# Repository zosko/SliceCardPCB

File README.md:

# Slice Card on PCB

### Scheme

### Board

### Preview

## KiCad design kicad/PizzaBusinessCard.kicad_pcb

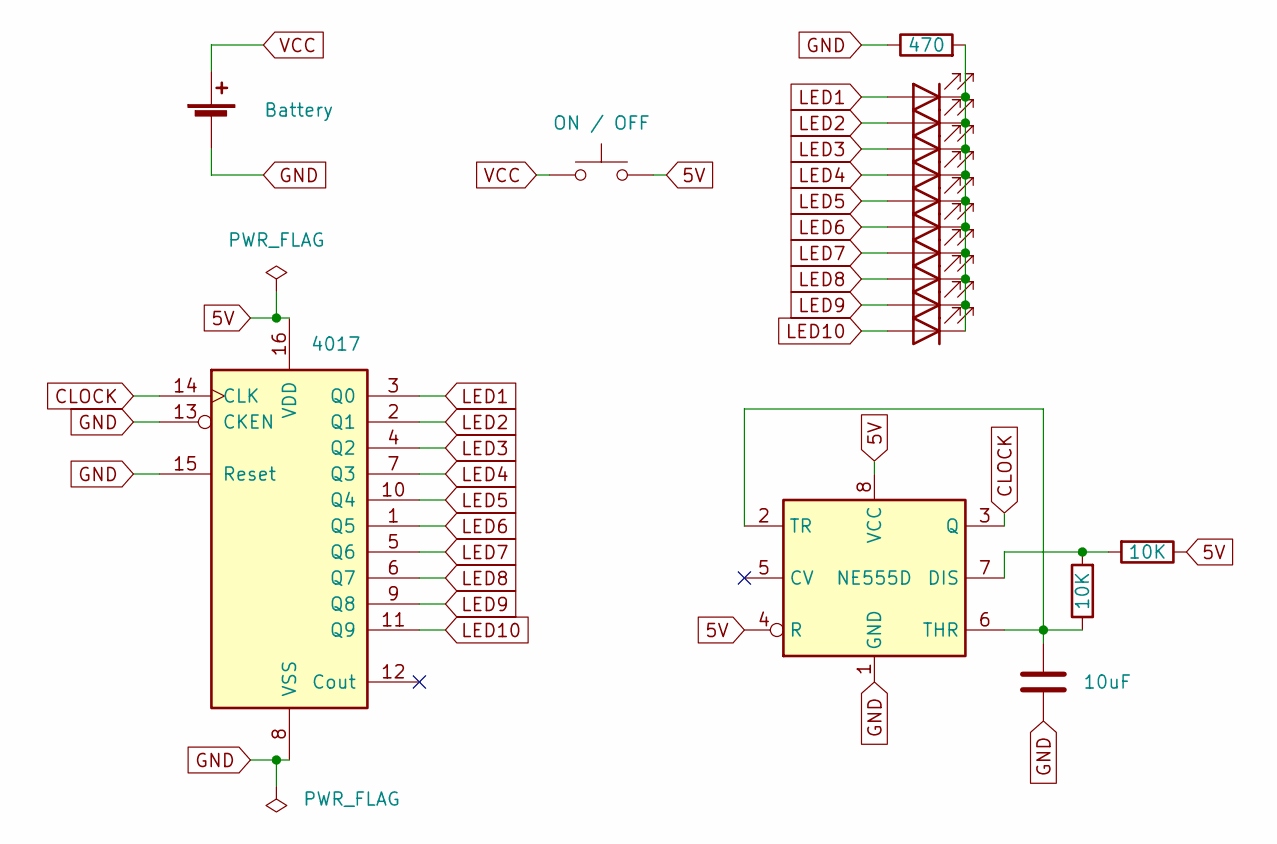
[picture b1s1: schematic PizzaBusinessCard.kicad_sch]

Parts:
BT1: Battery; BatteryHolder_Keystone_3000_1x12mm
C2: 10uF; C_0805_2012Metric_Pad1.18x1.45mm_HandSolder
D2, D3, D4, D5, D6, D7, D8, D9, D10, D11: LED; LED_0805_2012Metric_Pad1.15x1.40mm_HandSolder
R1, R3: 10K; R_0805_2012Metric_Pad1.20x1.40mm_HandSolder
R2: 470; R_0805_2012Metric_Pad1.20x1.40mm_HandSolder
SW1: ON / OFF; SW_SPST_CK_RS282G05A3
U1: 4017; SOIC-16_3.9x9.9mm_P1.27mm
U2: NE555D; SOIC-8_3.9x4.9mm_P1.27mm

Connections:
5V: R1.1, SW1.2, U1.16 (VDD), U2.4 (R), U2.8 (VCC)
CLOCK: U1.14 (CLK), U2.3 (Q)
GND: BT1.2 (-), C2.2, R2.1, U1.8 (VSS), U1.13 (CKEN), U1.15 (Reset), U2.1 (GND)
LED1: D2.2 (A), U1.3 (Q0)
LED2: D3.2 (A), U1.2 (Q1)
LED3: D4.2 (A), U1.4 (Q2)
LED4: D5.2 (A), U1.7 (Q3)
LED5: D6.2 (A), U1.10 (Q4)
LED6: D7.2 (A), U1.1 (Q5)
LED7: D8.2 (A), U1.5 (Q6)
LED8: D9.2 (A), U1.6 (Q7)
LED9: D10.2 (A), U1.9 (Q8)
LED10: D11.2 (A), U1.11 (Q9)
unnamed: C2.1, R3.1, U2.2 (TR), U2.6 (THR)
unnamed: D2.1 (K), D3.1 (K), D4.1 (K), D5.1 (K), D6.1 (K), D7.1 (K), D8.1 (K), D9.1 (K), D10.1 (K), D11.1 (K), R2.2
unnamed: R1.2, R3.2, U2.7 (DIS)
VCC: BT1.1 (+), SW1.1

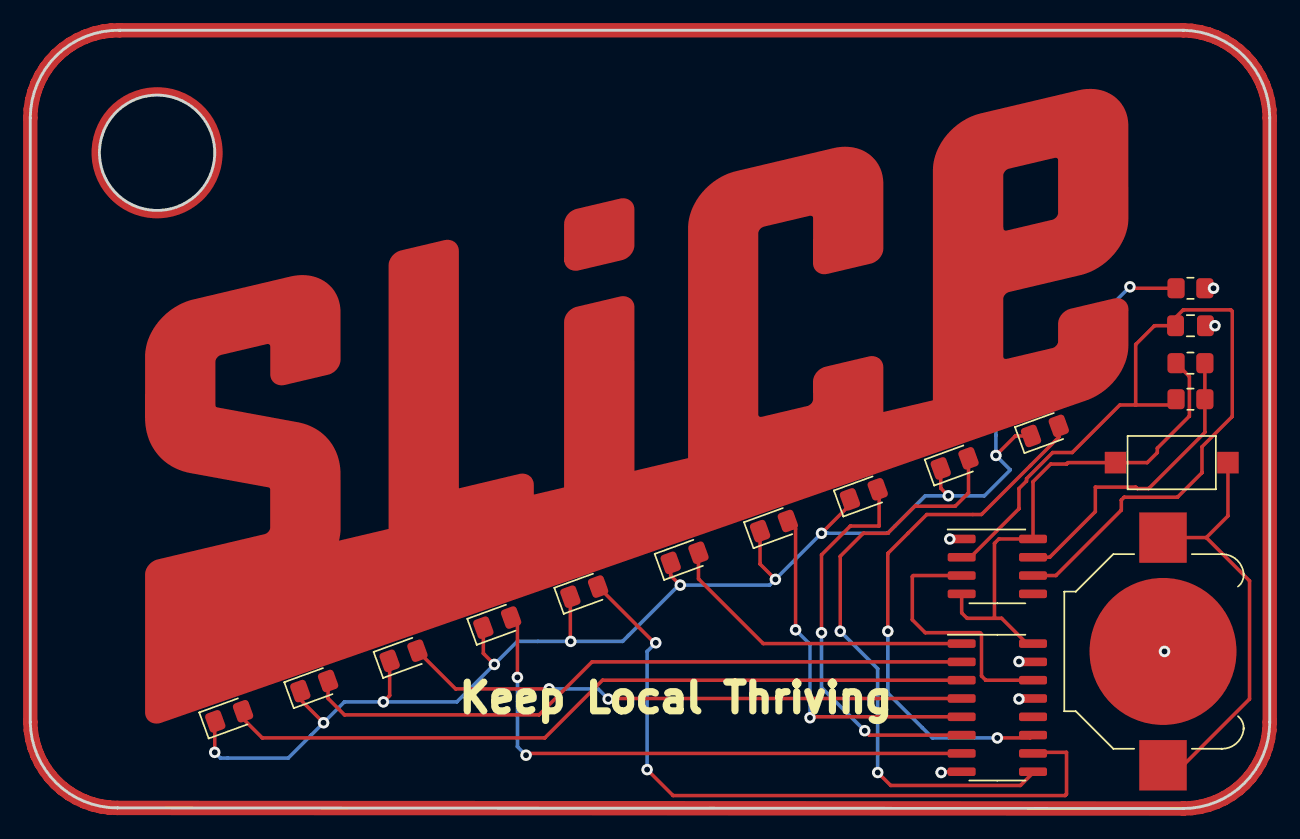
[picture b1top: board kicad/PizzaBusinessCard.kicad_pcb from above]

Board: 2 copper layers, 86.0 x 54.0 mm, 18 parts (0 on the bottom side), 17 nets.

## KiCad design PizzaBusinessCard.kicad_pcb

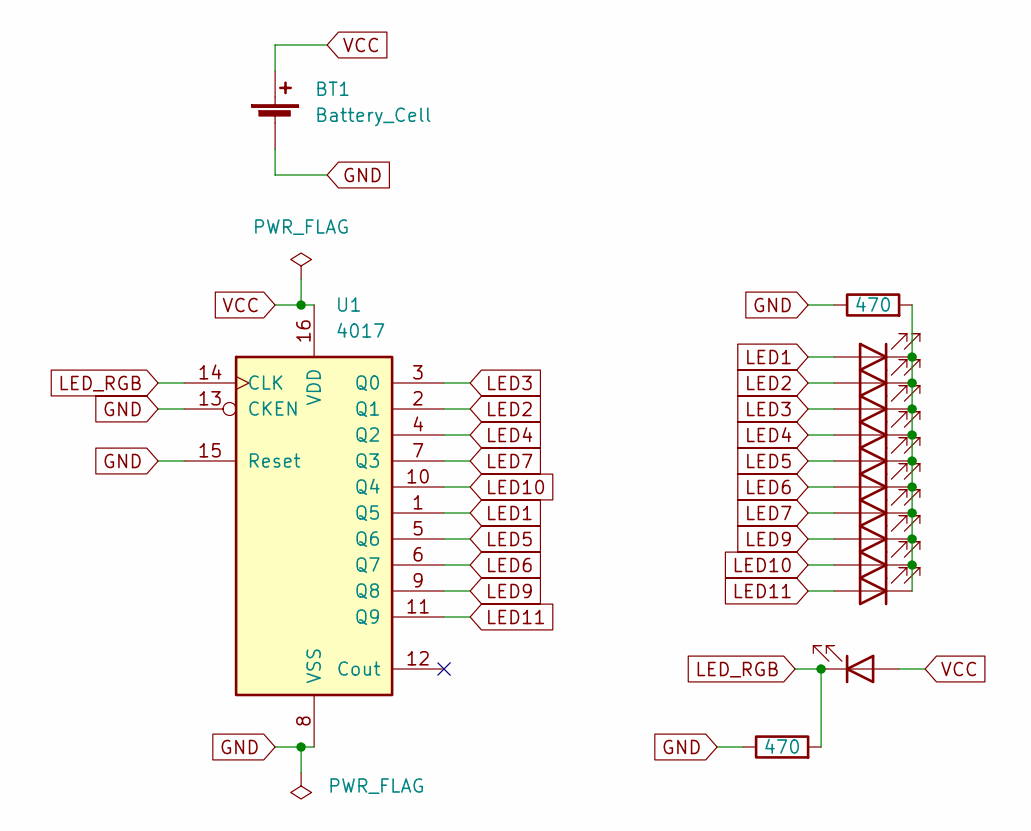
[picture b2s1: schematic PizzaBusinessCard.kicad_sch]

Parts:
BT1: Battery_Cell; BatteryHolder_Keystone_3000_1x12mm
D1, D2, D3, D4, D5, D6, D7, D8, D9, D10, D11: LED; LED_0805_2012Metric_Pad1.15x1.40mm_HandSolder
R1, R2: 470; R_0805_2012Metric_Pad1.20x1.40mm_HandSolder
U1: 4017; SOIC-16_3.9x9.9mm_P1.27mm

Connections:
GND: BT1.2 (-), R1.1, R2.1, U1.8 (VSS), U1.13 (CKEN), U1.15 (Reset)
LED1: D2.2 (A), U1.1 (Q5)
LED2: D3.2 (A), U1.2 (Q1)
LED3: D4.2 (A), U1.3 (Q0)
LED4: D5.2 (A), U1.4 (Q2)
LED5: D6.2 (A), U1.5 (Q6)
LED6: D7.2 (A), U1.6 (Q7)
LED7: D8.2 (A), U1.7 (Q3)
LED9: D9.2 (A), U1.9 (Q8)
LED10: D10.2 (A), U1.10 (Q4)
LED11: D11.2 (A), U1.11 (Q9)
LED_RGB: D1.1 (K), R1.2, U1.14 (CLK)
unnamed: D2.1 (K), D3.1 (K), D4.1 (K), D5.1 (K), D6.1 (K), D7.1 (K), D8.1 (K), D9.1 (K), D10.1 (K), D11.1 (K), R2.2
VCC: BT1.1 (+), D1.2 (A), U1.16 (VDD)

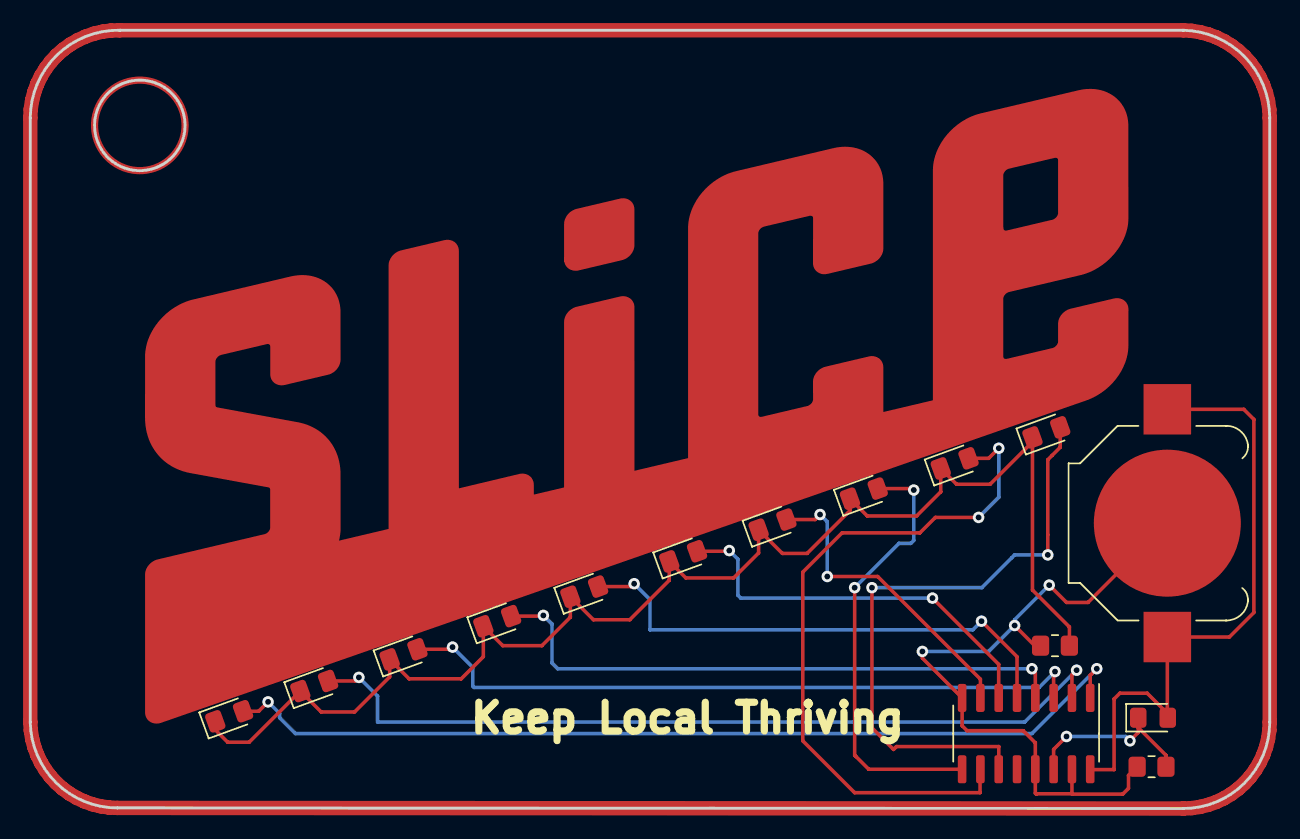
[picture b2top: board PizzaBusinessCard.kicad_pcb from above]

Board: 2 copper layers, 86.0 x 54.0 mm, 15 parts (0 on the bottom side), 14 nets.

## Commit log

2022-07-04 remove kicad
2022-07-04 add images
2022-07-04 update project
2022-07-04 gerbers
2022-09-16 implement with NE555
2022-09-17 simplify ne555
2022-09-18 fix ne555
2025-11-19 update to kicad 9
